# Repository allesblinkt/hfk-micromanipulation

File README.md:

# Micromanipulation

A workshop given for the Digital Media program of [HfK Bremen](https://www.hfk-bremen.de)

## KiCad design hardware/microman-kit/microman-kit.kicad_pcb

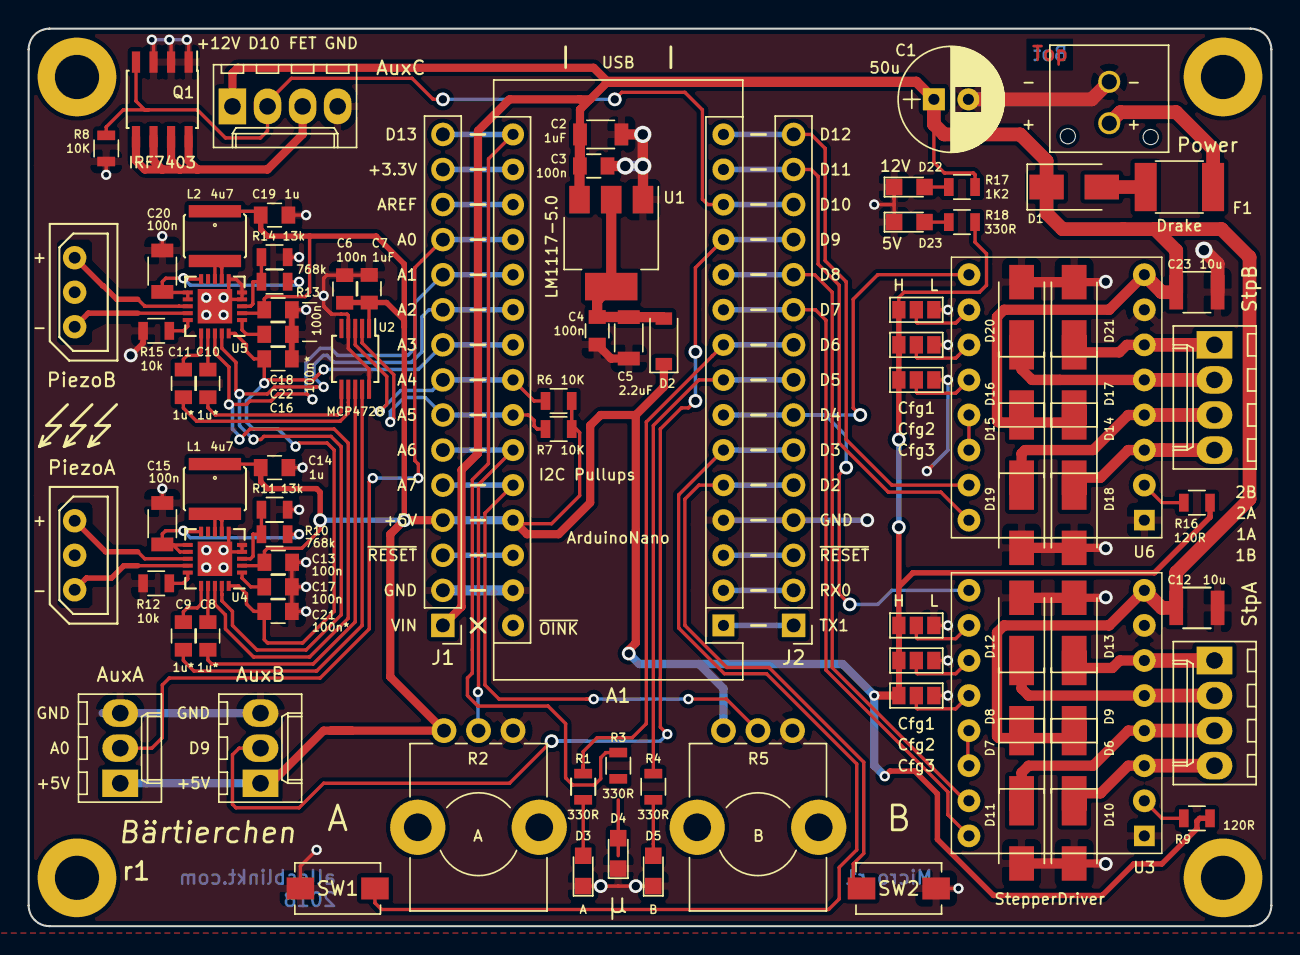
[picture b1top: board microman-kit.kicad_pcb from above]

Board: 2 copper layers, 90.0 x 65.0 mm, 97 parts (0 on the bottom side), 77 nets.

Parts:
A1: ArduinoNano; Arduino_Nano
C1: 50u; CP_Radial_D7.5mm_P2.50mm
C2: 1uF; C_1206
C3, C4, C7, C13, C17, C18, C22: 100n; C_0805
C5: 2.2uF; C_1206
C6: 1uF; C_0805
C8, C9, C10, C11: 1u*; C_0805
C12, C23: 10u; C_1210
C14, C19: 1u; C_0805
C15, C20: 100n; C_1206
C16, C21: 100n*; C_0805
D1: D_Schottky; D_SMA
D2: D_Schottky; D_SOD-123
D3: A; LED_0805
D4: μ; LED_0805
D5: B; LED_0805
D6, D7, D8, D9, D10, D11, D12, D13, D14, D15, D16, D17, D18, D19, D20, D21: Schot; D_SMA
D22: 12V; LED_0805
D23: 5V; LED_0805
F1: Drake; R_1812
HOLE1: 1; MountingHole_3.2mm_M3_ISO7380_Pad
HOLE2: 2; MountingHole_3.2mm_M3_ISO7380_Pad
HOLE3: 3; MountingHole_3.2mm_M3_ISO7380_Pad
HOLE4: 4; MountingHole_3.2mm_M3_ISO7380_Pad
J1: NanoHeaderA; Socket_Strip_Straight_1x15_Pitch2.54mm
J2: NanoHeaderB; Socket_Strip_Straight_1x15_Pitch2.54mm
J3: PiezoA; Molex_Spox_board_3pin
J4: PiezoB; Molex_Spox_board_3pin
J5: StpA; Molex_KK-6410-04_04x2.54mm_Straight
J6: StpB; Molex_KK-6410-04_04x2.54mm_Straight
J7: AuxA; Molex_KK-6410-03_03x2.54mm_Straight
J8: AuxB; Molex_KK-6410-03_03x2.54mm_Straight
J9: AuxC; Molex_KK-6410-04_04x2.54mm_Straight
J10, J13: Cfg1; GS3
J11, J14: Cfg2; GS3
J12, J15: Cfg3; GS3
L1, L2: 4u7; Coilcraft_LPS4018
P1: Power; Molex_Microfit3_Header_02x01_Straight_43045-0228
Q1: IRF7403; SOIC-8_3.9x4.9mm_Pitch1.27mm
R1, R3, R4, R18: 330R; R_0805
R2: A; Potentiometer_Alps_RK09K_Horizontal
R5: B; Potentiometer_Alps_RK09K_Horizontal
R6, R7, R8: 10K; R_0805
R9, R16: 120R; R_0805
R10, R13: 768k; R_0805
R11, R14: 13k; R_0805
R12, R15: 10k; R_0805
R17: 1K2; R_0805
SW1: A; SW_SPST_EVQPE1
SW2: B; SW_SPST_EVQPE1
U1: LM1117-5.0; SOT-223-3Lead_TabPin2
U2: MCP4728; MSOP-10_3x3mm_Pitch0.5mm
U3, U6: StepperDriver; SilentStepStick
U4, U5: DRV8662; QFN-20-1EP_4x4mm_Pitch0.5mm

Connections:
+3V3: A1.17, J1.14
+5V: A1.27, C6.1, C7.2, C13.2, C14.1, C18.2, C19.1, D2.1, J1.4, J7.1, J8.1, J10.1, J11.1, J12.1, J13.1, J14.1, J15.1, L1.1, L2.1, R2.1, R5.1, R6.1, R7.1, R9.1, R16.1, R18.1, U2.1, U4.2, U5.2
+12V: C1.1, C2.1, C3.2, C12.1, C23.1, D1.1, D6.1, D7.1, D8.1, D9.1, D14.1, D15.1, D16.1, D17.1, J1.1, J9.1, R17.1, U1.3, U3.8, U6.8
/A0: A1.19, J1.12, J7.2
/A1: A1.20, J1.11, U4.18, U5.18
/A2: A1.21, J1.10, U4.19, U5.19
/A3: A1.22, C16.2, C21.2, J1.9, U4.20, U5.20
/A4: A1.23, J1.8, R6.2, U2.3
/A5: A1.24, J1.7, R7.2, U2.2
/A6: A1.25, J1.6, R2.2
/A7: A1.26, J1.5, R5.2
/AREF: A1.18, J1.13
/AUX_B: A1.12, J2.12, J8.2
/AUX_C: A1.13, J2.13, J9.2, Q1.4, R8.1
/AxisDriverA/CFG1: J10.2, U3.10
/AxisDriverA/CFG2: J11.2, U3.11
/AxisDriverA/CFG3: J12.2, U3.12
/AxisDriverA/M_1A: D7.2, D11.1, J5.3, U3.4
/AxisDriverA/M_1B: D6.2, D10.1, J5.4, U3.3
/AxisDriverA/M_2A: D8.2, D12.1, J5.2, U3.5
/AxisDriverA/M_2B: D9.2, D13.1, J5.1, U3.6
/AxisDriverB/CFG1: J13.2, U6.10
/AxisDriverB/CFG2: J14.2, U6.11
/AxisDriverB/CFG3: J15.2, U6.12
/AxisDriverB/M_1A: D15.2, D19.1, J6.3, U6.4
/AxisDriverB/M_1B: D14.2, D18.1, J6.4, U6.3
/AxisDriverB/M_2A: D16.2, D20.1, J6.2, U6.5
/AxisDriverB/M_2B: D17.2, D21.1, J6.1, U6.6
/D0: A1.2, J2.2
/D1: A1.1, J2.1
/D2: A1.5, J2.5, SW2.1
/D3: A1.6, J2.6, SW1.1
/D4: A1.7, J2.7, U3.9, U6.9
/D5: A1.8, J2.8, R4.1
/D6: A1.9, J2.9, R1.1
/D7: A1.10, J2.10, U3.16
/D8: A1.11, J2.11, U3.15
/D11: A1.14, J2.14, U6.16
/D12: A1.15, J2.15, U6.15
/D13: A1.16, J1.15, R3.1
/DAC_A: C10.2, U2.6
/DAC_B: C11.2, U2.7
/DAC_C: C8.2, U2.8
/DAC_D: C9.2, U2.9
/PiezoDriverA/FB: R10.2, R11.1, U4.3
/PiezoDriverA/IN+: C8.1, U4.17
/PiezoDriverA/IN-: C9.1, U4.16
/PiezoDriverA/OUT+: J3.3, U4.13
/PiezoDriverA/OUT-: J3.1, U4.14
/PiezoDriverB/FB: R13.2, R14.1, U5.3
/PiezoDriverB/IN+: C10.1, U5.17
/PiezoDriverB/IN-: C11.1, U5.16
/PiezoDriverB/OUT+: J4.3, U5.13
/PiezoDriverB/OUT-: J4.1, U5.14
/~RESET: A1.3, A1.28, J1.3, J2.3
GND: A1.4, A1.29, C1.2, C2.2, C3.1, C4.1, C5.2, C6.2, C7.1, C12.2, C13.1, C14.2, C15.1, C16.1, C17.2, C18.1, C19.2, C20.1, C21.1, C22.2, C23.2, D3.1, D4.1, D5.1, D10.2, D11.2, D12.2, D13.2, D18.2, D19.2, D20.2, D21.2, D22.1, D23.1, J1.2, J2.4, J7.3, J8.3, J9.4, J10.3, J11.3, J12.3, J13.3, J14.3, J15.3, P1.1, Q1.1, Q1.2, Q1.3, R2.3, R5.3, R8.2, R11.2, R12.2, R14.2, R15.2, SW1.2, SW2.2, U1.1, U2.4, U2.10, U3.1, U3.7, U4.4, U4.5, U4.6, U4.21, U5.4, U5.5, U5.6, U5.21, U6.1, U6.7
unnamed: C4.2, C5.1, D2.2, U1.2
unnamed: C15.2, R10.1, U4.10, U4.11, U4.12
unnamed: C17.1, U4.1
unnamed: C20.2, R13.1, U5.10, U5.11, U5.12
unnamed: C22.1, U5.1
unnamed: D1.2, F1.1
unnamed: D3.2, R1.2
unnamed: D4.2, R3.2
unnamed: D5.2, R4.2
unnamed: D22.2, R17.2
unnamed: D23.2, R18.2
unnamed: F1.2, P1.2
unnamed: J9.3, Q1.5, Q1.6, Q1.7, Q1.8
unnamed: L1.2, U4.7, U4.8
unnamed: L2.2, U5.7, U5.8
unnamed: R9.2, U3.2
unnamed: R12.1, U4.15
unnamed: R15.1, U5.15
unnamed: R16.2, U6.2
unnamed: U3.13, U3.14
unnamed: U6.13, U6.14

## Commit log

2018-02-21 Added gitignore
2018-02-21 Added README
2018-02-21 Added starting points for code experiments
2018-02-21 Added cleaned Kit PCB
2018-02-21 Added schematic and PCB PDFs
2018-02-21 Added Gerber data
2018-02-21 Added modules and lib
2018-02-21 Added DRV8662
2018-02-21 kicad XML
2018-02-21 Added mechanical PCB
2018-02-21 Wrong README...
2018-02-21 Deleted wrong paragraph
2018-02-21 Added GPLv3 license
2018-02-22 Added introduction slides
2018-02-22 Removed filtering. Makes no sense
2018-02-25 Added Pi Camera microscope adaptor 3D files and STL
2018-02-25 Renamed files
2018-02-26 Added Processing sketch experiment for distributing seeds
2018-02-26 Added schedule
2018-02-28 Added Arduino serial read example
2018-03-01 Added HV supply trigger example
